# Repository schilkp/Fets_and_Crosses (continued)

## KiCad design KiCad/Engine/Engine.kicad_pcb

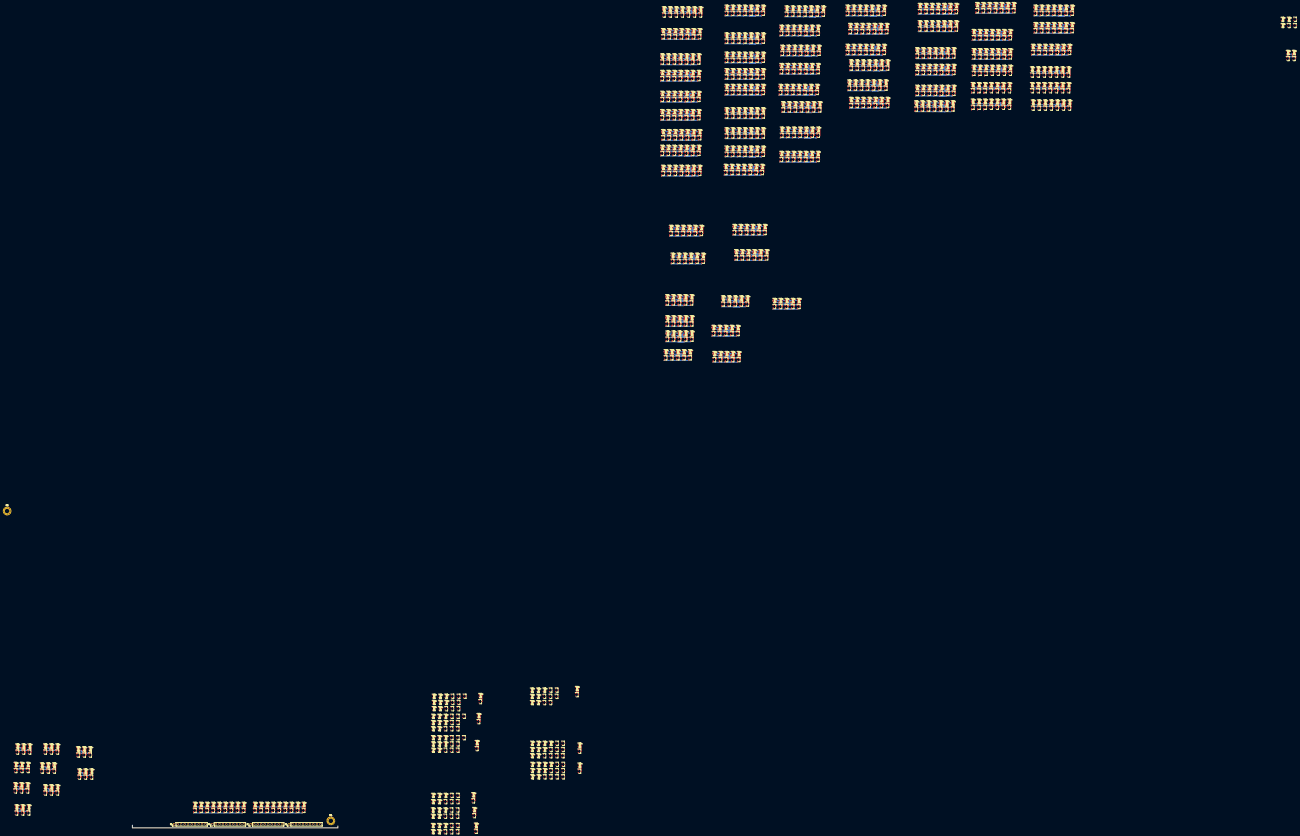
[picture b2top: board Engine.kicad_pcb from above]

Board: 2 copper layers, 149.9 x 1.9 mm, 1080 parts (0 on the bottom side), 567 nets.

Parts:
H1, H2: MountingHole; MountingHole_3.2mm_M3_Pad_Via
J1: Power; PinHeader_1x10_P2.54mm_Vertical
J3: P1; PinHeader_1x10_P2.54mm_Vertical
J4: P2; PinHeader_1x10_P2.54mm_Vertical
J5: Move; PinHeader_1x10_P2.54mm_Vertical
Q1, Q3, Q5, Q7, Q9, Q11, Q13, Q15, Q17, Q19, Q21, Q23, Q25, Q27, Q29, Q31, Q33, Q35, Q37, Q40, Q41, Q43, Q46, Q47, Q49, Q52, Q53, Q55, Q58, Q59, Q61, Q64, Q65, Q67, Q70, Q71, Q73, Q76, Q77, Q79, Q82, Q83, Q85, Q88, Q89, Q92, Q93, Q96, Q97, Q98, Q101, Q103, Q104, Q107, Q108, Q109, Q113, Q114, Q115, Q119, Q121, Q123, Q124, Q125, Q129, Q130, Q131, Q135, Q136, Q137, Q142, Q143, Q146, Q147, Q148, Q151, Q153, Q154, Q157, Q158, Q159, Q163, Q164, Q165, Q169, Q171, Q174, Q175, Q176, Q179, Q180, Q181, Q185, Q188, Q189, Q192, Q193, Q194, Q197, Q199, Q201, Q202, Q203, Q207, Q208, Q209, Q213, Q214, Q215, Q219, Q220, Q223, Q224, Q225, Q229, Q230, Q231, Q235, Q237, Q240, Q241, Q245, Q246, Q247, Q249, Q252, Q253, Q257, Q258, Q259, Q261, Q264, Q265, Q269, Q270, Q271, Q273, Q276, Q277, Q281, Q282, Q283, Q285, Q288, Q289, Q292, Q293, Q295, Q298, Q299, Q302, Q303, Q305, Q308, Q309, Q312, Q313, Q315, Q318, Q319, Q322, Q323, Q325, Q328, Q329, Q332, Q333, Q335, Q338, Q339, Q342, Q343, Q345, Q348, Q349, Q352, Q353, Q356, Q357, Q361, Q362, Q363, Q364, Q367, Q370, Q371, Q375, Q376, Q377, Q378, Q381, Q384, Q385, Q389, Q390, Q391, Q392, Q395, Q398, Q399, Q401, Q404, Q405, Q408, Q409, Q413, Q414, Q415, Q416, Q419, Q422, Q423, Q427, Q428, Q429, Q430, Q433, Q436, Q437, Q441, Q442, Q443, Q444, Q447, Q450, Q451, Q455, Q456, Q457, Q458, Q461, Q464, Q465, Q469, Q470, Q471, Q472, Q475, Q478, Q479, Q483, Q484, Q485, Q486, Q489, Q492, Q493, Q497, Q498, Q499, Q500, Q503, Q506, Q507, Q511, Q512, Q513, Q514, Q517, Q520, Q521, Q525, Q526, Q527, Q528, Q531, Q534, Q535, Q539, Q540, Q541, Q542, Q545, Q548, Q549, Q553, Q554, Q555, Q556, Q559, Q562, Q563, Q567, Q568, Q569, Q570, Q573, Q576, Q577, Q581, Q582, Q583, Q584, Q587, Q590, Q591, Q595, Q596, Q597, Q598, Q601, Q604, Q605, Q609, Q610, Q611, Q612, Q615, Q618, Q619, Q623, Q624, Q625, Q626, Q629, Q632, Q633, Q637, Q638, Q639, Q640, Q643, Q646, Q647, Q651, Q652, Q653, Q654, Q657, Q660, Q661, Q665, Q666, Q667, Q668, Q671, Q674, Q675, Q679, Q680, Q681, Q682, Q685, Q688, Q689, Q693, Q694, Q695, Q696, Q699, Q702, Q703, Q707, Q708, Q709, Q710, Q713, Q716, Q717, Q721, Q722, Q723, Q724, Q727, Q730, Q731, Q735, Q736, Q737, Q738, Q741, Q744, Q745, Q749, Q750, Q751, Q752, Q755, Q758, Q759, Q763, Q764, Q765, Q766, Q769, Q772, Q773, Q777, Q778, Q779, Q780, Q783, Q786, Q787, Q791, Q792, Q793, Q794, Q797, Q800, Q801, Q805, Q806, Q807, Q808, Q811, Q814, Q815, Q819, Q820, Q821, Q822, Q825, Q828, Q829, Q833, Q834, Q835, Q836, Q839, Q842, Q843, Q847, Q848, Q849, Q850, Q853, Q856, Q857, Q861, Q862, Q863, Q864, Q867, Q870, Q871, Q875, Q876, Q877, Q878, Q881, Q884, Q885, Q889, Q890, Q891, Q892, Q895, Q898, Q899, Q903, Q904, Q905, Q906, Q909, Q912, Q913, Q917, Q918, Q919, Q920, Q923, Q926, Q927, Q931, Q932, Q933, Q934, Q937, Q940, Q941, Q945, Q946, Q947, Q948, Q951, Q954, Q955, Q959, Q960, Q961, Q962, Q965, Q968, Q969, Q973, Q974, Q975, Q979, Q980, Q981, Q982, Q985, Q988, Q989, Q993, Q994, Q995, Q996, Q999, Q1002, Q1003, Q1007, Q1008, Q1009, Q1010, Q1013, Q1016, Q1017, Q1021, Q1022, Q1023, Q1024, Q1027, Q1030, Q1031, Q1035, Q1036, Q1037, Q1038, Q1041, Q1044, Q1045, Q1049, Q1050, Q1051, Q1052, Q1055, Q1058, Q1059, Q1063, Q1064, Q1065, Q1066, Q1069, Q1072, Q1073: BSS84; SOT-23-P
Q2, Q4, Q6, Q8, Q10, Q12, Q14, Q16, Q18, Q20, Q22, Q24, Q26, Q28, Q30, Q32, Q34, Q36, Q38, Q39, Q42, Q44, Q45, Q48, Q50, Q51, Q54, Q56, Q57, Q60, Q62, Q63, Q66, Q68, Q69, Q72, Q74, Q75, Q78, Q80, Q81, Q84, Q86, Q87, Q90, Q91, Q94, Q95, Q99, Q100, Q102, Q105, Q106, Q110, Q111, Q112, Q116, Q117, Q118, Q120, Q122, Q126, Q127, Q128, Q132, Q133, Q134, Q138, Q139, Q140, Q141, Q144, Q145, Q149, Q150, Q152, Q155, Q156, Q160, Q161, Q162, Q166, Q167, Q168, Q170, Q172, Q173, Q177, Q178, Q182, Q183, Q184, Q186, Q187, Q190, Q191, Q195, Q196, Q198, Q200, Q204, Q205, Q206, Q210, Q211, Q212, Q216, Q217, Q218, Q221, Q222, Q226, Q227, Q228, Q232, Q233, Q234, Q236, Q238, Q239, Q242, Q243, Q244, Q248, Q250, Q251, Q254, Q255, Q256, Q260, Q262, Q263, Q266, Q267, Q268, Q272, Q274, Q275, Q278, Q279, Q280, Q284, Q286, Q287, Q290, Q291, Q294, Q296, Q297, Q300, Q301, Q304, Q306, Q307, Q310, Q311, Q314, Q316, Q317, Q320, Q321, Q324, Q326, Q327, Q330, Q331, Q334, Q336, Q337, Q340, Q341, Q344, Q346, Q347, Q350, Q351, Q354, Q355, Q358, Q359, Q360, Q365, Q366, Q368, Q369, Q372, Q373, Q374, Q379, Q380, Q382, Q383, Q386, Q387, Q388, Q393, Q394, Q396, Q397, Q400, Q402, Q403, Q406, Q407, Q410, Q411, Q412, Q417, Q418, Q420, Q421, Q424, Q425, Q426, Q431, Q432, Q434, Q435, Q438, Q439, Q440, Q445, Q446, Q448, Q449, Q452, Q453, Q454, Q459, Q460, Q462, Q463, Q466, Q467, Q468, Q473, Q474, Q476, Q477, Q480, Q481, Q482, Q487, Q488, Q490, Q491, Q494, Q495, Q496, Q501, Q502, Q504, Q505, Q508, Q509, Q510, Q515, Q516, Q518, Q519, Q522, Q523, Q524, Q529, Q530, Q532, Q533, Q536, Q537, Q538, Q543, Q544, Q546, Q547, Q550, Q551, Q552, Q557, Q558, Q560, Q561, Q564, Q565, Q566, Q571, Q572, Q574, Q575, Q578, Q579, Q580, Q585, Q586, Q588, Q589, Q592, Q593, Q594, Q599, Q600, Q602, Q603, Q606, Q607, Q608, Q613, Q614, Q616, Q617, Q620, Q621, Q622, Q627, Q628, Q630, Q631, Q634, Q635, Q636, Q641, Q642, Q644, Q645, Q648, Q649, Q650, Q655, Q656, Q658, Q659, Q662, Q663, Q664, Q669, Q670, Q672, Q673, Q676, Q677, Q678, Q683, Q684, Q686, Q687, Q690, Q691, Q692, Q697, Q698, Q700, Q701, Q704, Q705, Q706, Q711, Q712, Q714, Q715, Q718, Q719, Q720, Q725, Q726, Q728, Q729, Q732, Q733, Q734, Q739, Q740, Q742, Q743, Q746, Q747, Q748, Q753, Q754, Q756, Q757, Q760, Q761, Q762, Q767, Q768, Q770, Q771, Q774, Q775, Q776, Q781, Q782, Q784, Q785, Q788, Q789, Q790, Q795, Q796, Q798, Q799, Q802, Q803, Q804, Q809, Q810, Q812, Q813, Q816, Q817, Q818, Q823, Q824, Q826, Q827, Q830, Q831, Q832, Q837, Q838, Q840, Q841, Q844, Q845, Q846, Q851, Q852, Q854, Q855, Q858, Q859, Q860, Q865, Q866, Q868, Q869, Q872, Q873, Q874, Q879, Q880, Q882, Q883, Q886, Q887, Q888, Q893, Q894, Q896, Q897, Q900, Q901, Q902, Q907, Q908, Q910, Q911, Q914, Q915, Q916, Q921, Q922, Q924, Q925, Q928, Q929, Q930, Q935, Q936, Q938, Q939, Q942, Q943, Q944, Q949, Q950, Q952, Q953, Q956, Q957, Q958, Q963, Q964, Q966, Q967, Q970, Q971, Q972, Q976, Q977, Q978, Q983, Q984, Q986, Q987, Q990, Q991, Q992, Q997, Q998, Q1000, Q1001, Q1004, Q1005, Q1006, Q1011, Q1012, Q1014, Q1015, Q1018, Q1019, Q1020, Q1025, Q1026, Q1028, Q1029, Q1032, Q1033, Q1034, Q1039, Q1040, Q1042, Q1043, Q1046, Q1047, Q1048, Q1053, Q1054, Q1056, Q1057, Q1060, Q1061, Q1062, Q1067, Q1068, Q1070, Q1071, Q1074: 2N7002; SOT-23-N

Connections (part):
+5V: J1.6, J1.7, J1.8, J1.9, J1.10, Q1.2, Q3.2, Q5.2, Q7.2, Q9.2, Q11.2, Q13.2, Q15.2, Q17.2, Q19.2, Q21.2, Q23.2, Q25.2, Q27.2, Q29.2, Q31.2, Q33.2, Q35.2, Q37.2, Q40.2, Q43.2, Q46.2, Q49.2, Q52.2, Q55.2, Q58.2, Q61.2, Q64.2, Q67.2, Q70.2, Q73.2, Q76.2, Q79.2, Q82.2, Q85.2, Q88.2, Q92.2, Q101.2, Q103.2, Q119.2, Q121.2, Q123.2, Q142.2, Q151.2, Q153.2, Q169.2, Q171.2, Q185.2, Q188.2, Q197.2, Q199.2, Q201.2, Q219.2, Q235.2, Q237.2, Q240.2, Q245.2, Q249.2, Q252.2, Q257.2, Q261.2, Q264.2, Q269.2, Q273.2, Q276.2, Q281.2, Q285.2, Q288.2, Q292.2, Q295.2, Q298.2, Q302.2, Q305.2, Q308.2, Q312.2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
/Board_P1_0: J3.10, Q1.1, Q2.1, Q39.1, Q40.1
/Board_P1_1: J3.9, Q3.1, Q4.1, Q45.1, Q46.1
/Board_P1_2: J3.8, Q5.1, Q6.1, Q51.1, Q52.1
/Board_P1_3: J3.7, Q7.1, Q8.1, Q57.1, Q58.1
/Board_P1_4: J3.6, Q9.1, Q10.1, Q63.1, Q64.1
/Board_P1_5: J3.5, Q11.1, Q12.1, Q69.1, Q70.1
/Board_P1_6: J3.4, Q13.1, Q14.1, Q75.1, Q76.1
/Board_P1_7: J3.3, Q15.1, Q16.1, Q81.1, Q82.1
/Board_P1_8: J3.2, Q17.1, Q18.1, Q87.1, Q88.1
/Board_P2_0: J4.10, Q19.1, Q20.1, Q41.1, Q42.1
/Board_P2_1: J4.9, Q21.1, Q22.1, Q47.1, Q48.1
/Board_P2_2: J4.8, Q23.1, Q24.1, Q53.1, Q54.1
/Board_P2_3: J4.7, Q25.1, Q26.1, Q59.1, Q60.1
/Board_P2_4: J4.6, Q27.1, Q28.1, Q65.1, Q66.1
/Board_P2_5: J4.5, Q29.1, Q30.1, Q71.1, Q72.1
/Board_P2_6: J4.4, Q31.1, Q32.1, Q77.1, Q78.1
/Board_P2_7: J4.3, Q33.1, Q34.1, Q83.1, Q84.1
/Board_P2_8: J4.2, Q35.1, Q36.1, Q89.1, Q90.1
/Computer0: J5.2, Q235.3, Q236.3
/Computer1: J5.3, Q197.3, Q198.3
/Computer2: J5.4, Q169.3, Q170.3
/Computer3: J5.5, Q151.3, Q152.3
/Computer4: J5.6, Q121.3, Q122.3
/Computer5: J5.7, Q101.3, Q102.3
/Computer6: J5.8, Q119.3, Q120.3
/Computer7: J5.9, Q185.3, Q186.3
/Computer8: J5.10, Q199.3, Q200.3
/M0_A: Q231.1, Q234.1, Q962.1, Q964.1, Q969.1, Q970.1, Q971.3, Q972.3, Q975.3, Q976.3
/M0_B: Q228.1, Q230.1, Q831.3, Q832.3, Q836.3, Q837.3, Q838.3, Q841.1, Q842.1
/M0_C: Q222.1, Q229.1, Q747.3, Q748.3, Q752.3, Q753.3, Q754.3, Q757.1, Q758.1
/M0_E: Q225.1, Q233.1, Q621.3, Q622.3, Q626.3, Q627.3, Q628.3, Q631.1, Q632.1
/M0_F: Q224.1, Q227.1, Q607.3, Q608.3, Q612.3, Q613.3, Q614.3, Q617.1, Q618.1
/M0_G: Q221.1, Q223.1, Q411.3, Q412.3, Q416.3, Q417.3, Q418.3, Q421.1, Q422.1
/M0_K: Q220.1, Q232.1, Q251.1, Q252.1, Q255.3, Q256.3, Q259.3, Q260.3
/M0_L: Q219.1, Q226.1, Q287.1, Q288.1, Q291.3, Q293.3, Q294.3
/M1_A: Q194.1, Q196.1, Q957.3, Q958.3, Q962.3, Q963.3, Q964.3, Q967.1, Q968.1
/M1_B: Q191.1, Q193.1, Q873.3, Q874.3, Q878.3, Q879.3, Q880.3, Q883.1, Q884.1
/M1_E: Q187.1, Q192.1, Q635.3, Q636.3, Q640.3, Q641.3, Q642.3, Q645.1, Q646.1
/M1_F: Q189.1, Q195.1, Q579.3, Q580.3, Q584.3, Q585.3, Q586.3, Q589.1, Q590.1
/M1_M: Q188.1, Q190.1, Q327.1, Q328.1, Q331.3, Q333.3, Q334.3
/M2_A: Q165.1, Q168.1, Q977.3, Q978.3, Q982.3, Q983.3, Q984.3, Q987.1, Q988.1
/M2_B: Q162.1, Q164.1, Q915.3, Q916.3, Q920.3, Q921.3, Q922.3, Q925.1, Q926.1
/M2_D: Q156.1, Q163.1, Q789.3, Q790.3, Q794.3, Q795.3, Q796.3, Q799.1, Q800.1
/M2_E: Q159.1, Q167.1, Q649.3, Q650.3, Q654.3, Q655.3, Q656.3, Q659.1, Q660.1
/M2_F: Q158.1, Q161.1, Q593.3, Q594.3, Q598.3, Q599.3, Q600.3, Q603.1, Q604.1
/M2_H: Q155.1, Q157.1, Q453.3, Q454.3, Q458.3, Q459.3, Q460.3, Q463.1, Q464.1
/M2_K: Q154.1, Q166.1, Q275.1, Q276.1, Q279.3, Q280.3, Q283.3, Q284.3
/M2_L: Q153.1, Q160.1, Q297.1, Q298.1, Q301.3, Q303.3, Q304.3
/M3_A: Q148.1, Q150.1, Q991.3, Q992.3, Q996.3, Q997.3, Q998.3, Q1001.1, Q1002.1
/M3_B: Q145.1, Q147.1, Q845.3, Q846.3, Q850.3, Q851.3, Q852.3, Q855.1, Q856.1
/M3_E: Q141.1, Q146.1, Q663.3, Q664.3, Q668.3, Q669.3, Q670.3, Q673.1, Q674.1
/M3_F: Q143.1, Q149.1, Q495.3, Q496.3, Q500.3, Q501.3, Q502.3, Q505.1, Q506.1
/M3_M: Q142.1, Q144.1, Q347.1, Q348.1, Q351.3, Q353.3, Q354.3
/M4_A: Q137.1, Q140.1, Q1005.3, Q1006.3, Q1010.3, Q1011.3, Q1012.3, Q1015.1, Q1016.1
/M4_B: Q134.1, Q136.1, Q887.3, Q888.3, Q892.3, Q893.3, Q894.3, Q897.1, Q898.1
/M4_C: Q128.1, Q135.1, Q761.3, Q762.3, Q766.3, Q767.3, Q768.3, Q771.1, Q772.1
/M4_D: Q131.1, Q139.1, Q803.3, Q804.3, Q808.3, Q809.3, Q810.3, Q813.1, Q814.1
/M4_E: Q130.1, Q133.1, Q677.3, Q678.3, Q682.3, Q683.3, Q684.3, Q687.1, Q688.1
/M4_F: Q127.1, Q129.1, Q523.3, Q524.3, Q528.3, Q529.3, Q530.3, Q533.1, Q534.1
/M4_G: Q125.1, Q138.1, Q425.3, Q426.3, Q430.3, Q431.3, Q432.3, Q435.1, Q436.1
/M4_H: Q124.1, Q132.1, Q467.3, Q468.3, Q472.3, Q473.3, Q474.3, Q477.1, Q478.1
/M4_I: Q123.1, Q126.1, Q403.1, Q404.1, Q407.3, Q409.3, Q410.3
/M5_A: Q98.1, Q100.1, Q1019.3, Q1020.3, Q1024.3, Q1025.3, Q1026.3, Q1029.1, Q1030.1
/M5_B: Q95.1, Q97.1, Q929.3, Q930.3, Q934.3, Q935.3, Q936.3, Q939.1, Q940.1
/M5_E: Q91.1, Q96.1, Q691.3, Q692.3, Q696.3, Q697.3, Q698.3, Q701.1, Q702.1
/M5_F: Q93.1, Q99.1, Q551.3, Q552.3, Q556.3, Q557.3, Q558.3, Q561.1, Q562.1
/M5_M: Q92.1, Q94.1, Q337.1, Q338.1, Q341.3, Q343.3, Q344.3
/M6_A: Q115.1, Q118.1, Q1033.3, Q1034.3, Q1038.3, Q1039.3, Q1040.3, Q1043.1, Q1044.1
/M6_B: Q112.1, Q114.1, Q859.3, Q860.3, Q864.3, Q865.3, Q866.3, Q869.1, Q870.1
/M6_D: Q106.1, Q113.1, Q817.3, Q818.3, Q822.3, Q823.3, Q824.3, Q827.1, Q828.1
/M6_E: Q109.1, Q117.1, Q705.3, Q706.3, Q710.3, Q711.3, Q712.3, Q715.1, Q716.1
/M6_F: Q108.1, Q111.1, Q509.3, Q510.3, Q514.3, Q515.3, Q516.3, Q519.1, Q520.1
/M6_H: Q105.1, Q107.1, Q481.3, Q482.3, Q486.3, Q487.3, Q488.3, Q491.1, Q492.1
/M6_K: Q104.1, Q116.1, Q239.1, Q240.1, Q243.3, Q244.3, Q247.3, Q248.3
/M6_L: Q103.1, Q110.1, Q307.1, Q308.1, Q311.3, Q313.3, Q314.3
/M7_A: Q181.1, Q184.1, Q1047.3, Q1048.3, Q1052.3, Q1053.3, Q1054.3, Q1057.1, Q1058.1
/M7_B: Q178.1, Q180.1, Q901.3, Q902.3, Q906.3, Q907.3, Q908.3, Q911.1, Q912.1
/M7_E: Q173.1, Q179.1, Q719.3, Q720.3, Q724.3, Q725.3, Q726.3, Q729.1, Q730.1
/M7_F: Q176.1, Q183.1, Q537.3, Q538.3, Q542.3, Q543.3, Q544.3, Q547.1, Q548.1
/M7_I: Q175.1, Q177.1, Q359.3, Q360.3, Q364.3, Q365.3, Q366.3, Q369.1, Q370.1
/M7_J: Q172.1, Q174.1, Q373.3, Q374.3, Q378.3, Q379.3, Q380.3, Q383.1, Q384.1
/M7_M: Q171.1, Q182.1, Q355.3, Q357.3, Q358.3
/M8_A: Q215.1, Q218.1, Q1061.3, Q1062.3, Q1066.3, Q1067.3, Q1068.3, Q1071.1, Q1072.1
/M8_B: Q212.1, Q214.1, Q943.3, Q944.3, Q948.3, Q949.3, Q950.3, Q953.1, Q954.1
/M8_C: Q206.1, Q213.1, Q775.3, Q776.3, Q780.3, Q781.3, Q782.3, Q785.1, Q786.1
/M8_E: Q209.1, Q217.1, Q733.3, Q734.3, Q738.3, Q739.3, Q740.3, Q743.1, Q744.1
/M8_F: Q208.1, Q211.1, Q565.3, Q566.3, Q570.3, Q571.3, Q572.3, Q575.1, Q576.1
/M8_G: Q205.1, Q207.1, Q439.3, Q440.3, Q444.3, Q445.3, Q446.3, Q449.1, Q450.1
/M8_I: Q203.1, Q216.1, Q387.3, Q388.3, Q392.3, Q393.3, Q394.3, Q397.1, Q398.1
/M8_K: Q202.1, Q210.1, Q263.1, Q264.1, Q267.3, Q268.3, Q271.3, Q272.3
/M8_L: Q201.1, Q204.1, Q317.1, Q318.1, Q321.3, Q323.3, Q324.3
/Sheet60D62401/sheet60D63D17/A: Q221.3, Q222.3, Q226.3, Q227.3, Q228.3, Q231.3, Q232.3, Q233.3, Q234.3, Q235.1, Q236.1
/Sheet6047D39E/OUT0: Q1.3, Q2.3, Q267.1, Q269.1, Q359.1, Q361.1, Q425.1, Q427.1, Q439.1, Q441.1, Q495.1, Q497.1, Q509.1, Q511.1, Q635.1, Q637.1, Q649.1, Q651.1
/Sheet6047D39E/OUT1: Q3.3, Q4.3, Q523.1, Q525.1, Q537.1, Q539.1, Q621.1, Q623.1, Q650.1, Q652.1
/Sheet6047D39E/OUT2: Q5.3, Q6.3, Q243.1, Q245.1, Q373.1, Q375.1, Q467.1, Q469.1, Q481.1, Q483.1, Q551.1, Q553.1, Q565.1, Q567.1, Q622.1, Q624.1, Q636.1, Q638.1
/Sheet6047D39E/OUT3: Q7.3, Q8.3, Q510.1, Q512.1, Q607.1, Q609.1, Q677.1, Q679.1, Q691.1, Q693.1
/Sheet6047D39E/OUT4: Q9.3, Q10.3, Q411.1, Q413.1, Q440.1, Q442.1, Q453.1, Q455.1, Q482.1, Q484.1, Q538.1, Q540.1, Q579.1, Q581.1, Q663.1, Q665.1, Q692.1, Q694.1
/Sheet6047D39E/OUT5: Q11.3, Q12.3, Q387.1, Q389.1, Q566.1, Q568.1, Q593.1, Q595.1, Q664.1, Q666.1, Q678.1, Q680.1
/Sheet6047D39E/OUT6: Q13.3, Q14.3, Q279.1, Q281.1, Q374.1, Q376.1, Q454.1, Q456.1, Q468.1, Q470.1, Q496.1, Q498.1, Q608.1, Q610.1, Q719.1, Q721.1, Q733.1, Q735.1
/Sheet6047D39E/OUT7: Q15.3, Q16.3, Q388.1, Q390.1, Q524.1, Q526.1, Q580.1, Q582.1, Q705.1, Q707.1, Q734.1, Q736.1
/Sheet6047D39E/OUT8: Q17.3, Q18.3, Q255.1, Q257.1, Q360.1, Q362.1, Q412.1, Q414.1, Q426.1, Q428.1, Q552.1, Q554.1, Q594.1, Q596.1, Q706.1, Q708.1, Q720.1, Q722.1
/Sheet6049469B/Q0: Q37.3, Q38.3, Q256.1, Q258.1, Q291.1, Q292.1, Q415.1, Q417.1, Q611.1, Q613.1, Q625.1, Q627.1, Q751.1, Q753.1, Q835.1, Q837.1, Q975.1, Q976.1
/Sheet6049469B/Q1: Q43.3, Q44.3, Q331.1, Q332.1, Q583.1, Q585.1, Q639.1, Q641.1, Q877.1, Q879.1, Q961.1, Q963.1
/Sheet6049469B/Q2: Q49.3, Q50.3, Q280.1, Q282.1, Q301.1, Q302.1, Q457.1, Q459.1, Q597.1, Q599.1, Q653.1, Q655.1, Q793.1, Q795.1, Q919.1, Q921.1, Q981.1, Q983.1
/Sheet6049469B/Q3: Q55.3, Q56.3, Q351.1, Q352.1, Q499.1, Q501.1, Q667.1, Q669.1, Q849.1, Q851.1, Q995.1, Q997.1
/Sheet6049469B/Q4: Q61.3, Q62.3, Q407.1, Q408.1, Q429.1, Q431.1, Q471.1, Q473.1, Q527.1, Q529.1, Q681.1, Q683.1, Q765.1, Q767.1, Q807.1, Q809.1, Q891.1, Q893.1, Q1009.1, Q1011.1
/Sheet6049469B/Q5: Q67.3, Q68.3, Q341.1, Q342.1, Q555.1, Q557.1, Q695.1, Q697.1, Q933.1, Q935.1, Q1023.1, Q1025.1
/Sheet6049469B/Q6: Q73.3, Q74.3, Q244.1, Q246.1, Q311.1, Q312.1, Q485.1, Q487.1, Q513.1, Q515.1, Q709.1, Q711.1, Q821.1, Q823.1, Q863.1, Q865.1, Q1037.1, Q1039.1
/Sheet6049469B/Q7: Q79.3, Q80.3, Q357.1, Q358.1, Q363.1, Q365.1, Q377.1, Q379.1, Q541.1, Q543.1, Q723.1, Q725.1, Q905.1, Q907.1, Q1051.1, Q1053.1
/Sheet6049469B/Q8: Q85.3, Q86.3, Q268.1, Q270.1, Q321.1, Q322.1, Q391.1, Q393.1, Q443.1, Q445.1, Q569.1, Q571.1, Q737.1, Q739.1, Q779.1, Q781.1, Q947.1, Q949.1, Q1065.1, Q1067.1
/Sheet6049469B/Sheet60506E58/sheet5E562435/A: Q37.1, Q38.1, Q39.3, Q41.3, Q42.3
/Sheet6049469B/sheet6050A891/sheet5E562435/A: Q85.1, Q86.1, Q87.3, Q89.3, Q90.3
/Sheet6049469B/sheet60509B33/sheet5E562435/A: Q61.1, Q62.1, Q63.3, Q65.3, Q66.3
/Sheet6049469B/sheet60509B34/sheet5E562435/A: Q67.1, Q68.1, Q69.3, Q71.3, Q72.3
/Sheet6049469B/sheet60509B35/sheet5E562435/A: Q73.1, Q74.1, Q75.3, Q77.3, Q78.3
/Sheet6049469B/sheet60509B36/sheet5E562435/A: Q79.1, Q80.1, Q81.3, Q83.3, Q84.3
/Sheet6049469B/sheet605078C4/sheet5E562435/A: Q43.1, Q44.1, Q45.3, Q47.3, Q48.3
/Sheet6049469B/sheet60508995/sheet5E562435/A: Q49.1, Q50.1, Q51.3, Q53.3, Q54.3
/Sheet6049469B/sheet60508996/sheet5E562435/A: Q55.1, Q56.1, Q57.3, Q59.3, Q60.3
/Sheet60494411/Sheet604ADE57/sheet6054A98B/sheet5E562435/A: Q965.1, Q966.1, Q967.3, Q969.3, Q970.3
/Sheet60494411/sheet606FAE28/Block: Q965.3, Q966.3, Q982.1, Q984.1, Q989.1, Q990.1
/Sheet60494411/sheet606FAE28/sheet6054A98B/sheet5E562435/A: Q985.1, Q986.1, Q987.3, Q989.3, Q990.3
/Sheet60494411/sheet606FDE93/Block: Q985.3, Q986.3, Q996.1, Q998.1, Q1003.1, Q1004.1
/Sheet60494411/sheet606FDE93/sheet6054A98B/sheet5E562435/A: Q999.1, Q1000.1, Q1001.3, Q1003.3, Q1004.3
/Sheet60494411/sheet60700FC2/Block: Q999.3, Q1000.3, Q1010.1, Q1012.1, Q1017.1, Q1018.1
/Sheet60494411/sheet60700FC2/sheet6054A98B/sheet5E562435/A: Q1013.1, Q1014.1, Q1015.3, Q1017.3, Q1018.3
/Sheet60494411/sheet60703EAC/Block: Q1013.3, Q1014.3, Q1024.1, Q1026.1, Q1031.1, Q1032.1
/Sheet60494411/sheet60703EAC/sheet6054A98B/sheet5E562435/A: Q1027.1, Q1028.1, Q1029.3, Q1031.3, Q1032.3
/Sheet60494411/sheet60707A9A/Block: Q1027.3, Q1028.3, Q1038.1, Q1040.1, Q1045.1, Q1046.1
/Sheet60494411/sheet60707A9A/sheet6054A98B/sheet5E562435/A: Q1041.1, Q1042.1, Q1043.3, Q1045.3, Q1046.3
/Sheet60494411/sheet60707A9B/Block: Q1041.3, Q1042.3, Q1052.1, Q1054.1, Q1059.1, Q1060.1
/Sheet60494411/sheet60707A9B/sheet6054A98B/sheet5E562435/A: Q1055.1, Q1056.1, Q1057.3, Q1059.3, Q1060.3
/Sheet60494411/sheet60707A9C/Block: Q1055.3, Q1056.3, Q1066.1, Q1068.1, Q1073.1, Q1074.1
/Sheet60494411/sheet60707A9C/sheet6054A98B/sheet5E562435/A: Q1069.1, Q1070.1, Q1071.3, Q1073.3, Q1074.3
/sheet60D7BB73/sheet60D63D17/A: Q187.3, Q190.3, Q191.3, Q194.3, Q195.3, Q196.3, Q197.1, Q198.1
/sheet60D69699/sheet60D63D17/A: Q199.1, Q200.1, Q204.3, Q205.3, Q206.3, Q210.3, Q211.3, Q212.3, Q215.3, Q216.3, Q217.3, Q218.3
/sheet60D98711/sheet60D63D17/A: Q172.3, Q173.3, Q177.3, Q178.3, Q181.3, Q182.3, Q183.3, Q184.3, Q185.1, Q186.1
/sheet60DD6E3C/sheet60D63D17/A: Q155.3, Q156.3, Q160.3, Q161.3, Q162.3, Q165.3, Q166.3, Q167.3, Q168.3, Q169.1, Q170.1
/sheet60DF89F7/sheet60D63D17/A: Q141.3, Q144.3, Q145.3, Q148.3, Q149.3, Q150.3, Q151.1, Q152.1
/sheet60E0A4D6/sheet60D63D17/A: Q121.1, Q122.1, Q126.3, Q127.3, Q128.3, Q132.3, Q133.3, Q134.3, Q137.3, Q138.3, Q139.3, Q140.3
/sheet60E1B2DC/sheet60D63D17/A: Q91.3, Q94.3, Q95.3, Q98.3, Q99.3, Q100.3, Q101.1, Q102.1
/sheet60E2C560/sheet60D63D17/A: Q105.3, Q106.3, Q110.3, Q111.3, Q112.3, Q115.3, Q116.3, Q117.3, Q118.3, Q119.1, Q120.1
/sheet604A8195/Inhib: Q741.3, Q742.3
/sheet604A8195/sheet6057F84C/Block: Q500.1, Q502.1, Q507.1, Q508.1
/sheet604A8195/sheet6057F84C/Block_Out: Q503.3, Q504.3
/sheet604A8195/sheet6057F84C/sheet6054A98B/sheet5E562435/A: Q503.1, Q504.1, Q505.3, Q507.3, Q508.3
/sheet604A8195/sheet6057F84E/Block: Q514.1, Q516.1, Q521.1, Q522.1
/sheet604A8195/sheet6057F84E/Block_Out: Q517.3, Q518.3
/sheet604A8195/sheet6057F84E/sheet6054A98B/sheet5E562435/A: Q517.1, Q518.1, Q519.3, Q521.3, Q522.3
/sheet604A8195/sheet6057F84F/Block: Q528.1, Q530.1, Q535.1, Q536.1
/sheet604A8195/sheet6057F84F/Block_Out: Q531.3, Q532.3
/sheet604A8195/sheet6057F84F/sheet6054A98B/sheet5E562435/A: Q531.1, Q532.1, Q533.3, Q535.3, Q536.3
/sheet604A8195/sheet6057F850/Block: Q542.1, Q544.1, Q549.1, Q550.1
/sheet604A8195/sheet6057F850/Block_Out: Q545.3, Q546.3
/sheet604A8195/sheet6057F850/sheet6054A98B/sheet5E562435/A: Q545.1, Q546.1, Q547.3, Q549.3, Q550.3
/sheet604A8195/sheet6057F851/Block: Q556.1, Q558.1, Q563.1, Q564.1
/sheet604A8195/sheet6057F851/Block_Out: Q559.3, Q560.3
/sheet604A8195/sheet6057F851/sheet6054A98B/sheet5E562435/A: Q559.1, Q560.1, Q561.3, Q563.3, Q564.3
/sheet604A8195/sheet6057F852/Block: Q570.1, Q572.1, Q577.1, Q578.1
/sheet604A8195/sheet6057F852/Block_Out: Q573.3, Q574.3
/sheet604A8195/sheet6057F852/sheet6054A98B/sheet5E562435/A: Q573.1, Q574.1, Q575.3, Q577.3, Q578.3
/sheet604A8195/sheet6057F853/Block: Q584.1, Q586.1, Q591.1, Q592.1
/sheet604A8195/sheet6057F853/Block_Out: Q587.3, Q588.3
/sheet604A8195/sheet6057F853/sheet6054A98B/sheet5E562435/A: Q587.1, Q588.1, Q589.3, Q591.3, Q592.3
/sheet604A8195/sheet6057F854/Block: Q598.1, Q600.1, Q605.1, Q606.1
/sheet604A8195/sheet6057F854/Block_Out: Q601.3, Q602.3
/sheet604A8195/sheet6057F854/sheet6054A98B/sheet5E562435/A: Q601.1, Q602.1, Q603.3, Q605.3, Q606.3
/sheet604A8195/sheet605862BA/Block: Q612.1, Q614.1, Q619.1, Q620.1
/sheet604A8195/sheet605862BA/Block_Out: Q615.3, Q616.3
/sheet604A8195/sheet605862BA/sheet6054A98B/sheet5E562435/A: Q615.1, Q616.1, Q617.3, Q619.3, Q620.3
/sheet606A7B7E/Inhib: Q626.1, Q628.1, Q633.1, Q634.1, Q825.3, Q826.3
/sheet606A7B7E/sheet606E673A/Block: Q629.3, Q630.3, Q640.1, Q642.1, Q647.1, Q648.1
/sheet606A7B7E/sheet606E673A/sheet6054A98B/sheet5E562435/A: Q643.1, Q644.1, Q645.3, Q647.3, Q648.3
/sheet606A7B7E/sheet606E673B/Block: Q643.3, Q644.3, Q654.1, Q656.1, Q661.1, Q662.1
/sheet606A7B7E/sheet606E673B/sheet6054A98B/sheet5E562435/A: Q657.1, Q658.1, Q659.3, Q661.3, Q662.3
/sheet606A7B7E/sheet606E673C/Block: Q657.3, Q658.3, Q668.1, Q670.1, Q675.1, Q676.1
/sheet606A7B7E/sheet606E673C/sheet6054A98B/sheet5E562435/A: Q671.1, Q672.1, Q673.3, Q675.3, Q676.3
/sheet606A7B7E/sheet606E673D/Block: Q671.3, Q672.3, Q682.1, Q684.1, Q689.1, Q690.1
/sheet606A7B7E/sheet606E673D/sheet6054A98B/sheet5E562435/A: Q685.1, Q686.1, Q687.3, Q689.3, Q690.3
/sheet606A7B7E/sheet606E673E/Block: Q685.3, Q686.3, Q696.1, Q698.1, Q703.1, Q704.1
/sheet606A7B7E/sheet606E673E/sheet6054A98B/sheet5E562435/A: Q699.1, Q700.1, Q701.3, Q703.3, Q704.3
/sheet606A7B7E/sheet606E6739/sheet6054A98B/sheet5E562435/A: Q629.1, Q630.1, Q631.3, Q633.3, Q634.3
/sheet606A7B7E/sheet606EA29D/Block: Q699.3, Q700.3, Q710.1, Q712.1, Q717.1, Q718.1
/sheet606A7B7E/sheet606EA29D/sheet6054A98B/sheet5E562435/A: Q713.1, Q714.1, Q715.3, Q717.3, Q718.3
/sheet606A7B7E/sheet606EA29E/Block: Q713.3, Q714.3, Q724.1, Q726.1, Q731.1, Q732.1
/sheet606A7B7E/sheet606EA29E/sheet6054A98B/sheet5E562435/A: Q727.1, Q728.1, Q729.3, Q731.3, Q732.3
/sheet606A7B7E/sheet606EA29F/Block: Q727.3, Q728.3, Q738.1, Q740.1, Q745.1, Q746.1
/sheet606A7B7E/sheet606EA29F/sheet6054A98B/sheet5E562435/A: Q741.1, Q742.1, Q743.3, Q745.3, Q746.3
/sheet607BECBB/Inhib: Q315.3, Q316.3, Q329.1, Q330.1, Q333.1, Q334.1
/sheet607BECBB/sheet607A4A2C/Block: Q325.3, Q326.3, Q349.1, Q350.1, Q353.1, Q354.1
/sheet607BECBB/sheet607A4A2C/sheet6054A98B/sheet5E562435/A: Q345.1, Q346.1, Q347.3, Q349.3, Q350.3
/sheet607BECBB/sheet607A6A47/Block: Q339.1, Q340.1, Q343.1, Q344.1, Q345.3, Q346.3
/sheet607BECBB/sheet607A6A47/sheet6054A98B/sheet5E562435/A: Q335.1, Q336.1, Q337.3, Q339.3, Q340.3
/sheet607BECBB/sheet607A3999/sheet6054A98B/sheet5E562435/A: Q325.1, Q326.1, Q327.3, Q329.3, Q330.3
/sheet607BECBB/sheet6087B8C1/A: Q335.3, Q336.3, Q355.1, Q356.1
/sheet6055E6A3/Inhib: Q836.1, Q838.1, Q843.1, Q844.1, Q1069.3, Q1070.3
/sheet6055E6A3/sheet606C7A55/Block: Q909.3, Q910.3, Q920.1, Q922.1, Q927.1, Q928.1
/sheet6055E6A3/sheet606C7A55/sheet6054A98B/sheet5E562435/A: Q923.1, Q924.1, Q925.3, Q927.3, Q928.3
/sheet6055E6A3/sheet606C7A56/Block: Q923.3, Q924.3, Q934.1, Q936.1, Q941.1, Q942.1
/sheet6055E6A3/sheet606C7A56/sheet6054A98B/sheet5E562435/A: Q937.1, Q938.1, Q939.3, Q941.3, Q942.3
/sheet6055E6A3/sheet606C7A57/Block: Q937.3, Q938.3, Q948.1, Q950.1, Q955.1, Q956.1
/sheet6055E6A3/sheet606C7A57/sheet6054A98B/sheet5E562435/A: Q951.1, Q952.1, Q953.3, Q955.3, Q956.3
/sheet6055E6A3/sheet6071E22D/Block: Q867.3, Q868.3, Q878.1, Q880.1, Q885.1, Q886.1
/sheet6055E6A3/sheet6071E22D/sheet6054A98B/sheet5E562435/A: Q881.1, Q882.1, Q883.3, Q885.3, Q886.3
/sheet6055E6A3/sheet6071E22E/Block: Q881.3, Q882.3, Q892.1, Q894.1, Q899.1, Q900.1
/sheet6055E6A3/sheet6071E22E/sheet6054A98B/sheet5E562435/A: Q895.1, Q896.1, Q897.3, Q899.3, Q900.3
/sheet6055E6A3/sheet6071E22F/Block: Q895.3, Q896.3, Q906.1, Q908.1, Q913.1, Q914.1
/sheet6055E6A3/sheet6071E22F/sheet6054A98B/sheet5E562435/A: Q909.1, Q910.1, Q911.3, Q913.3, Q914.3
/sheet6055E6A3/sheet60719C5D/sheet6054A98B/sheet5E562435/A: Q839.1, Q840.1, Q841.3, Q843.3, Q844.3
/sheet6055E6A3/sheet60719C5E/Block: Q839.3, Q840.3, Q850.1, Q852.1, Q857.1, Q858.1
/sheet6055E6A3/sheet60719C5E/sheet6054A98B/sheet5E562435/A: Q853.1, Q854.1, Q855.3, Q857.3, Q858.3
/sheet6055E6A3/sheet60719C5F/Block: Q853.3, Q854.3, Q864.1, Q866.1, Q871.1, Q872.1
/sheet6055E6A3/sheet60719C5F/sheet6054A98B/sheet5E562435/A: Q867.1, Q868.1, Q869.3, Q871.3, Q872.3
/sheet6058F8AB/Inhib: Q752.1, Q754.1, Q759.1, Q760.1, Q951.3, Q952.3
/sheet6058F8AB/sheet606D52B7/sheet6054A98B/sheet5E562435/A: Q755.1, Q756.1, Q757.3, Q759.3, Q760.3
/sheet6058F8AB/sheet606D52B8/Block: Q755.3, Q756.3, Q766.1, Q768.1, Q773.1, Q774.1
/sheet6058F8AB/sheet606D52B8/sheet6054A98B/sheet5E562435/A: Q769.1, Q770.1, Q771.3, Q773.3, Q774.3
/sheet6058F8AB/sheet606D52B9/Block: Q769.3, Q770.3, Q780.1, Q782.1, Q787.1, Q788.1
/sheet6058F8AB/sheet606D52B9/sheet6054A98B/sheet5E562435/A: Q783.1, Q784.1, Q785.3, Q787.3, Q788.3
/sheet6058F8AB/sheet606D52BA/Block: Q783.3, Q784.3, Q794.1, Q796.1, Q801.1, Q802.1
/sheet6058F8AB/sheet606D52BA/sheet6054A98B/sheet5E562435/A: Q797.1, Q798.1, Q799.3, Q801.3, Q802.3
/sheet6058F8AB/sheet606D52BB/Block: Q797.3, Q798.3, Q808.1, Q810.1, Q815.1, Q816.1
/sheet6058F8AB/sheet606D52BB/sheet6054A98B/sheet5E562435/A: Q811.1, Q812.1, Q813.3, Q815.3, Q816.3
/sheet6058F8AB/sheet606D52BC/Block: Q811.3, Q812.3, Q822.1, Q824.1, Q829.1, Q830.1
/sheet6058F8AB/sheet606D52BC/sheet6054A98B/sheet5E562435/A: Q825.1, Q826.1, Q827.3, Q829.3, Q830.3
/sheet6073F2C8/Inhib: Q364.1, Q366.1, Q371.1, Q372.1, Q489.3, Q490.3
/sheet6073F2C8/sheet606FFAAD/sheet6054A98B/sheet5E562435/A: Q367.1, Q368.1, Q369.3, Q371.3, Q372.3
/sheet6073F2C8/sheet606FFAAE/Block: Q367.3, Q368.3, Q378.1, Q380.1, Q385.1, Q386.1
/sheet6073F2C8/sheet606FFAAE/sheet6054A98B/sheet5E562435/A: Q381.1, Q382.1, Q383.3, Q385.3, Q386.3
/sheet6073F2C8/sheet606FFAAF/Block: Q381.3, Q382.3, Q392.1, Q394.1, Q399.1, Q400.1
/sheet6073F2C8/sheet606FFAAF/sheet6054A98B/sheet5E562435/A: Q395.1, Q396.1, Q397.3, Q399.3, Q400.3
/sheet6073F2C8/sheet60758AB2/Block: Q395.3, Q396.3, Q405.1, Q406.1, Q409.1, Q410.1
/sheet6073F2C8/sheet60758AB2/sheet6054A98B/sheet5E562435/A: Q401.1, Q402.1, Q403.3, Q405.3, Q406.3
/sheet6079A94F/Inhib: Q237.3, Q238.3, Q289.1, Q290.1, Q293.1, Q294.1
/sheet6079A94F/sheet607A4A2C/Block: Q305.3, Q306.3, Q319.1, Q320.1, Q323.1, Q324.1
/sheet6079A94F/sheet607A4A2C/sheet6054A98B/sheet5E562435/A: Q315.1, Q316.1, Q317.3, Q319.3, Q320.3
/sheet6079A94F/sheet607A6A47/Block: Q285.3, Q286.3, Q299.1, Q300.1, Q303.1, Q304.1
/sheet6079A94F/sheet607A6A47/sheet6054A98B/sheet5E562435/A: Q295.1, Q296.1, Q297.3, Q299.3, Q300.3
/sheet6079A94F/sheet607A7A7B/Block: Q295.3, Q296.3, Q309.1, Q310.1, Q313.1, Q314.1
/sheet6079A94F/sheet607A7A7B/sheet6054A98B/sheet5E562435/A: Q305.1, Q306.1, Q307.3, Q309.3, Q310.3
/sheet6079A94F/sheet607A3999/sheet6054A98B/sheet5E562435/A: Q285.1, Q286.1, Q287.3, Q289.3, Q290.3
/sheet60491C71/OUT0: Q19.3, Q20.3, Q761.1, Q763.1, Q775.1, Q777.1, Q845.1, Q847.1, Q859.1, Q861.1, Q957.1, Q959.1, Q977.1, Q979.1
/sheet60491C71/OUT1: Q21.3, Q22.3, Q887.1, Q889.1, Q901.1, Q903.1, Q971.1, Q973.1, Q978.1, Q980.1
/sheet60491C71/OUT2: Q23.3, Q24.3, Q803.1, Q805.1, Q817.1, Q819.1, Q929.1, Q931.1, Q943.1, Q945.1, Q958.1, Q960.1, Q972.1, Q974.1
/sheet60491C71/OUT3: Q25.3, Q26.3, Q831.1, Q833.1, Q860.1, Q862.1, Q1005.1, Q1007.1, Q1019.1, Q1021.1
/sheet60491C71/OUT4: Q27.3, Q28.3, Q747.1, Q749.1, Q776.1, Q778.1, Q789.1, Q791.1, Q818.1, Q820.1, Q873.1, Q875.1, Q902.1, Q904.1, Q991.1, Q993.1, Q1020.1, Q1022.1
/sheet60491C71/OUT5: Q29.3, Q30.3, Q915.1, Q917.1, Q944.1, Q946.1, Q992.1, Q994.1, Q1006.1, Q1008.1
/sheet60491C71/OUT6: Q31.3, Q32.3, Q790.1, Q792.1, Q804.1, Q806.1, Q832.1, Q834.1, Q846.1, Q848.1, Q1047.1, Q1049.1, Q1061.1, Q1063.1
/sheet60491C71/OUT7: Q33.3, Q34.3, Q874.1, Q876.1, Q888.1, Q890.1, Q1033.1, Q1035.1, Q1062.1, Q1064.1
/sheet60491C71/OUT8: Q35.3, Q36.3, Q748.1, Q750.1, Q762.1, Q764.1, Q916.1, Q918.1, Q930.1, Q932.1, Q1034.1, Q1036.1, Q1048.1, Q1050.1
/sheet606933A1/Inhib: Q416.1, Q418.1, Q423.1, Q424.1
/sheet606933A1/sheet606F7BEA/sheet6054A98B/sheet5E562435/A: Q419.1, Q420.1, Q421.3, Q423.3, Q424.3
/sheet606933A1/sheet606F7BEB/Block: Q419.3, Q420.3, Q430.1, Q432.1, Q437.1, Q438.1
/sheet606933A1/sheet606F7BEB/sheet6054A98B/sheet5E562435/A: Q433.1, Q434.1, Q435.3, Q437.3, Q438.3
/sheet606933A1/sheet606F7BEC/Block: Q433.3, Q434.3, Q444.1, Q446.1, Q451.1, Q452.1
/sheet606933A1/sheet606F7BEC/sheet6054A98B/sheet5E562435/A: Q447.1, Q448.1, Q449.3, Q451.3, Q452.3
/sheet606933A1/sheet606FA47B/Block: Q447.3, Q448.3, Q458.1, Q460.1, Q465.1, Q466.1
/sheet606933A1/sheet606FA47B/sheet6054A98B/sheet5E562435/A: Q461.1, Q462.1, Q463.3, Q465.3, Q466.3
/sheet606933A1/sheet606FA47C/Block: Q461.3, Q462.3, Q472.1, Q474.1, Q479.1, Q480.1
/sheet606933A1/sheet606FA47C/sheet6054A98B/sheet5E562435/A: Q475.1, Q476.1, Q477.3, Q479.3, Q480.3
/sheet606933A1/sheet606FA47D/Block: Q475.3, Q476.3, Q486.1, Q488.1, Q493.1, Q494.1
/sheet606933A1/sheet606FA47D/sheet6054A98B/sheet5E562435/A: Q489.1, Q490.1, Q491.3, Q493.3, Q494.3
/sheet60779195/Inhib: Q253.1, Q254.1, Q259.1, Q260.1, Q401.3, Q402.3
/sheet60779195/sheet6077F4BF/Block: Q241.1, Q242.1, Q247.1, Q248.1, Q273.3, Q274.3
/sheet60779195/sheet6077F4BF/sheet6054A98B/sheet5E562435/A: Q237.1, Q238.1, Q239.3, Q241.3, Q242.3
/sheet60779195/sheet60781DDC/Block: Q249.3, Q250.3, Q265.1, Q266.1, Q271.1, Q272.1
/sheet60779195/sheet60781DDC/sheet6054A98B/sheet5E562435/A: Q261.1, Q262.1, Q263.3, Q265.3, Q266.3
/sheet60779195/sheet60781390/sheet6054A98B/sheet5E562435/A: Q249.1, Q250.1, Q251.3, Q253.3, Q254.3
/sheet60779195/sheet60782894/Block: Q261.3, Q262.3, Q277.1, Q278.1, Q283.1, Q284.1
/sheet60779195/sheet60782894/sheet6054A98B/sheet5E562435/A: Q273.1, Q274.1, Q275.3, Q277.3, Q278.3
GND: J1.1, J1.2, J1.3, J1.4, J1.5, J3.1, J4.1, J5.1, Q2.2, Q4.2, Q6.2, Q8.2, Q10.2, Q12.2, Q14.2, Q16.2, Q18.2, Q20.2, Q22.2, Q24.2, Q26.2, Q28.2, Q30.2, Q32.2, Q34.2, Q36.2, Q38.2, Q39.2, Q42.2, Q44.2, Q45.2, Q48.2, Q50.2, Q51.2, Q54.2, Q56.2, Q57.2, Q60.2, Q62.2, Q63.2, Q66.2, Q68.2, Q69.2, Q72.2, Q74.2, Q75.2, Q78.2, Q80.2, Q81.2, Q84.2, Q86.2, Q87.2, Q90.2, Q91.2, Q94.2, Q95.2, Q99.2, Q100.2, Q102.2, Q105.2, Q106.2, Q110.2, Q111.2, Q112.2, Q116.2, Q117.2, Q118.2, Q120.2, Q122.2, Q126.2, Q127.2, Q128.2, Q132.2, Q133.2, Q134.2, Q138.2, Q139.2, Q140.2, Q141.2, Q144.2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
unnamed: Q40.3, Q41.2
unnamed: Q46.3, Q47.2
unnamed: Q52.3, Q53.2
unnamed: Q58.3, Q59.2
unnamed: Q64.3, Q65.2
unnamed: Q70.3, Q71.2
unnamed: Q76.3, Q77.2
unnamed: Q82.3, Q83.2
unnamed: Q88.3, Q89.2
unnamed: Q92.3, Q93.2
unnamed: Q93.3, Q96.2
unnamed: Q96.3, Q97.2
unnamed: Q97.3, Q98.2
unnamed: Q103.3, Q104.2
unnamed: Q104.3, Q107.2
unnamed: Q107.3, Q108.2
unnamed: Q108.3, Q109.2
unnamed: Q109.3, Q113.2
unnamed: Q113.3, Q114.2
unnamed: Q114.3, Q115.2
unnamed: Q123.3, Q124.2
unnamed: Q124.3, Q125.2
unnamed: Q125.3, Q129.2
unnamed: Q129.3, Q130.2
unnamed: Q130.3, Q131.2
unnamed: Q131.3, Q135.2
unnamed: Q135.3, Q136.2
unnamed: Q136.3, Q137.2
unnamed: Q142.3, Q143.2
unnamed: Q143.3, Q146.2
unnamed: Q146.3, Q147.2
unnamed: Q147.3, Q148.2
unnamed: Q153.3, Q154.2
unnamed: Q154.3, Q157.2
unnamed: Q157.3, Q158.2
unnamed: Q158.3, Q159.2
unnamed: Q159.3, Q163.2
unnamed: Q163.3, Q164.2
unnamed: Q164.3, Q165.2
unnamed: Q171.3, Q174.2
unnamed: Q174.3, Q175.2
unnamed: Q175.3, Q176.2
unnamed: Q176.3, Q179.2
unnamed: Q179.3, Q180.2
unnamed: Q180.3, Q181.2
unnamed: Q188.3, Q189.2
unnamed: Q189.3, Q192.2
unnamed: Q192.3, Q193.2
unnamed: Q193.3, Q194.2
unnamed: Q201.3, Q202.2
unnamed: Q202.3, Q203.2
unnamed: Q203.3, Q207.2
unnamed: Q207.3, Q208.2
unnamed: Q208.3, Q209.2
unnamed: Q209.3, Q213.2
unnamed: Q213.3, Q214.2
unnamed: Q214.3, Q215.2
unnamed: Q219.3, Q220.2
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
